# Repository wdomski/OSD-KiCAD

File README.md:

# OSD-KiCAD
LM1881 based separator for OSD

This example project shows implementation of OSD (on screen device) 
based on LM1881. 

The project was created with KiCAD.

Some more detail about the project and usage with RP2040 Raspberry Pi microcontroller 
can be found on my blog 
[On-screen Display with Raspberry Pi Pico](https://blog.domski.pl/on-screen-display-with-raspberry-pi-pico/).

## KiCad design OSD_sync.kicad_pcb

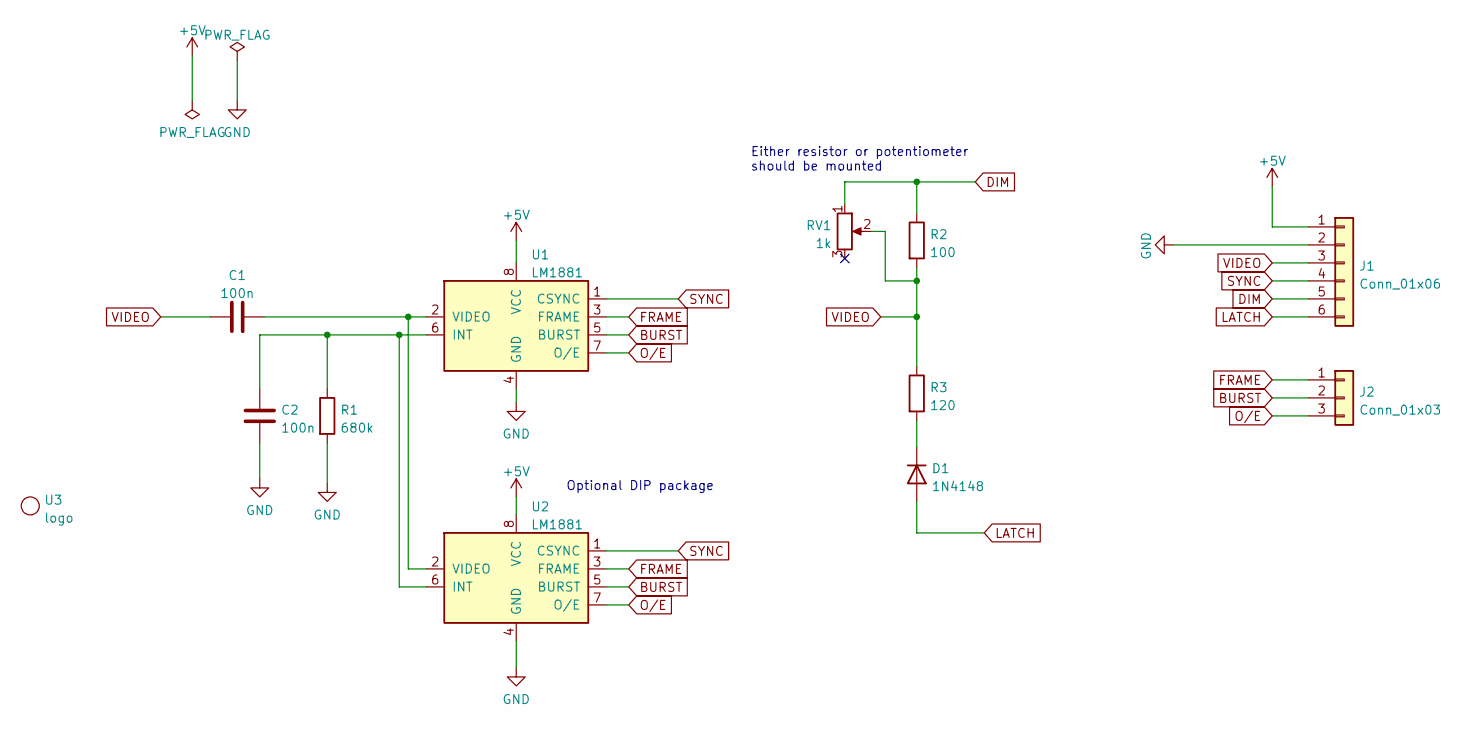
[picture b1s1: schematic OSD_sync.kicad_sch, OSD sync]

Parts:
C1, C2: 100n; C_0603_1608Metric_Pad1.08x0.95mm_HandSolder
D1: 1N4148; D_1206_3216Metric
J1: Conn_01x06; PinHeader_1x06_P2.54mm_Vertical
J2: Conn_01x03; PinHeader_1x03_P2.54mm_Vertical
R1: 680k; R_0603_1608Metric_Pad0.98x0.95mm_HandSolder
R2: 100; R_0603_1608Metric_Pad0.98x0.95mm_HandSolder
R3: 120; R_0603_1608Metric_Pad0.98x0.95mm_HandSolder
RV1: 1k; Potentiometer_Bourns_3296W_Vertical
U1: LM1881; SOIC-8_3.9x4.9mm_P1.27mm
U2: LM1881; DIP-8_W7.62mm
U3: logo; LOGO_100

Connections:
+5V: J1.1, U1.8 (VCC), U2.8 (VCC)
BURST: J2.2, U1.5 (BURST), U2.5 (BURST)
DIM: J1.5, R2.1, RV1.1
FRAME: J2.1, U1.3 (FRAME), U2.3 (FRAME)
GND: C2.2, J1.2, R1.2, U1.4 (GND), U2.4 (GND)
LATCH: D1.2 (A), J1.6
unnamed: D1.1 (K), R3.2
unnamed: C2.1, R1.1, U1.6 (INT), U2.6 (INT)
unnamed: C1.2, U1.2 (VIDEO), U2.2 (VIDEO)
O/E: J2.3, U1.7 (O/E), U2.7 (O/E)
SYNC: J1.4, U1.1 (CSYNC), U2.1 (CSYNC)
VIDEO: C1.1, J1.3, R2.2, R3.1, RV1.2

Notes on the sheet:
Optional DIP package
Either resistor or potentiometer should be mounted

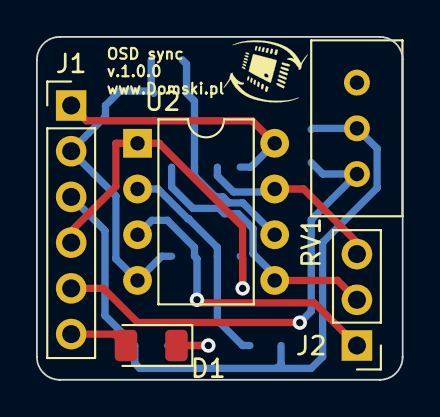
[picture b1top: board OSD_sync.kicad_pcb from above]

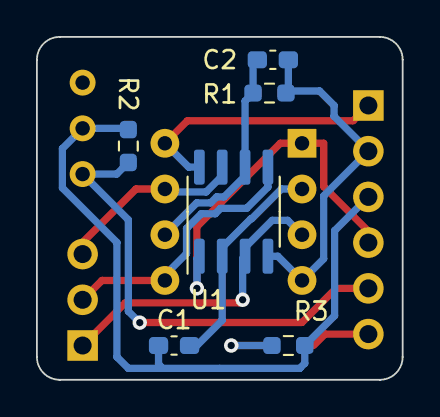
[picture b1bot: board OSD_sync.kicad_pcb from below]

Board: 2 copper layers, 20.3 x 19.1 mm, 12 parts (6 on the bottom side), 12 nets.

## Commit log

2023-12-28 Added KiCAD project
2024-01-25 Added README file
